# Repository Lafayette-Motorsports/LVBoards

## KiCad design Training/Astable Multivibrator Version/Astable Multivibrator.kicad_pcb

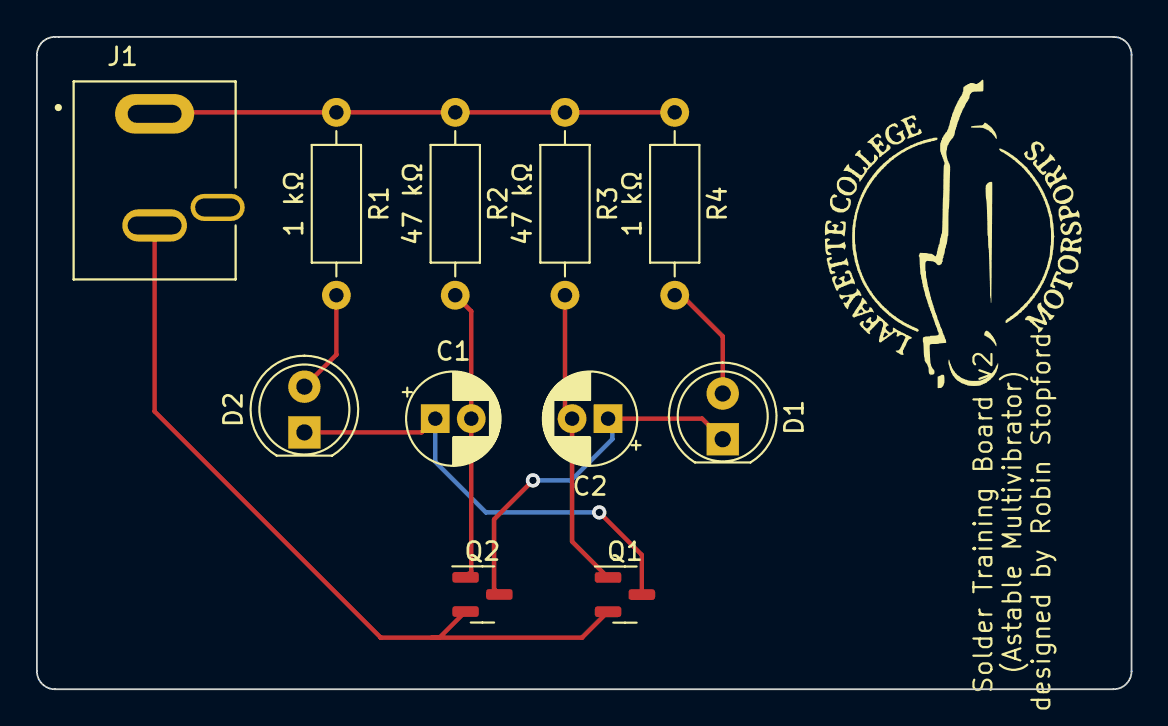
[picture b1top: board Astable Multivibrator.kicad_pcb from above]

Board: 2 copper layers, 60.8 x 36.2 mm, 11 parts (0 on the bottom side), 8 nets.

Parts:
C1, C2: 10uF; CP_Radial_D5.0mm_P2.00mm
D1, D2: LED; LED_D5.0mm
J1: 5V; CUI_PJ-044A
Q1, Q2: MMBT3904; SOT-23
R1, R4: 1 kΩ; R_Axial_DIN0207_L6.3mm_D2.5mm_P10.16mm_Horizontal
R2, R3: 47 kΩ; R_Axial_DIN0207_L6.3mm_D2.5mm_P10.16mm_Horizontal

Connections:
GND: J1.2, Q1.2 (E), Q2.2 (E)
unnamed: D1.2 (A), R4.2
unnamed: C2.1, D1.1 (K), Q2.3 (C)
unnamed: D2.2 (A), R1.2
unnamed: C1.1, D2.1 (K), Q1.3 (C)
unnamed: J1.1, R1.1, R2.1, R3.1, R4.1
unnamed: C2.2, Q1.1 (B), R3.2
unnamed: C1.2, Q2.1 (B), R2.2

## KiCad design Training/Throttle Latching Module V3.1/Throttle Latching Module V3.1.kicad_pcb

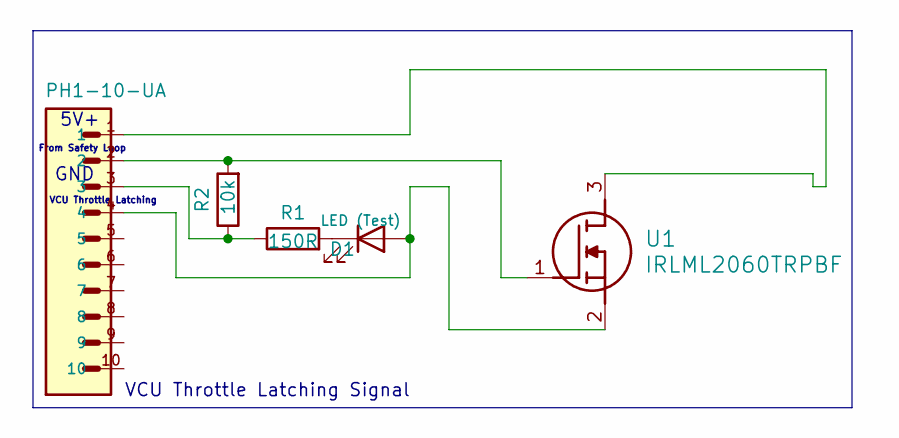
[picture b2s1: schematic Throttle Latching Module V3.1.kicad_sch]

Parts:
D1: LED (Test); LED_0603_1608Metric
J1: PH1-10-UA; JST_PH_B12B-PH-K_1x12_P2.00mm_Vertical
R1: 150R; R_Axial_DIN0204_L3.6mm_D1.6mm_P7.62mm_Horizontal
R2: 10k; R_Axial_DIN0204_L3.6mm_D1.6mm_P7.62mm_Horizontal
U1: IRLML2060TRPBF; SOT95P237X112-3N; Manufacturer_Part_Number IRLML2060TRPBF; Mouser Part Number 942-IRLML2060TRPBF

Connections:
unnamed: D1.2 (A), J1.4, U1.2 (S)
unnamed: D1.1 (K), R1.2
unnamed: J1.3, R1.1, R2.1
unnamed: J1.1, U1.3 (D)
unnamed: J1.2, R2.2, U1.1 (G)

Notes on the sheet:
5V+
VCU Throttle Latching
VCU Throttle Latching Signal
From Safety Loop
GND

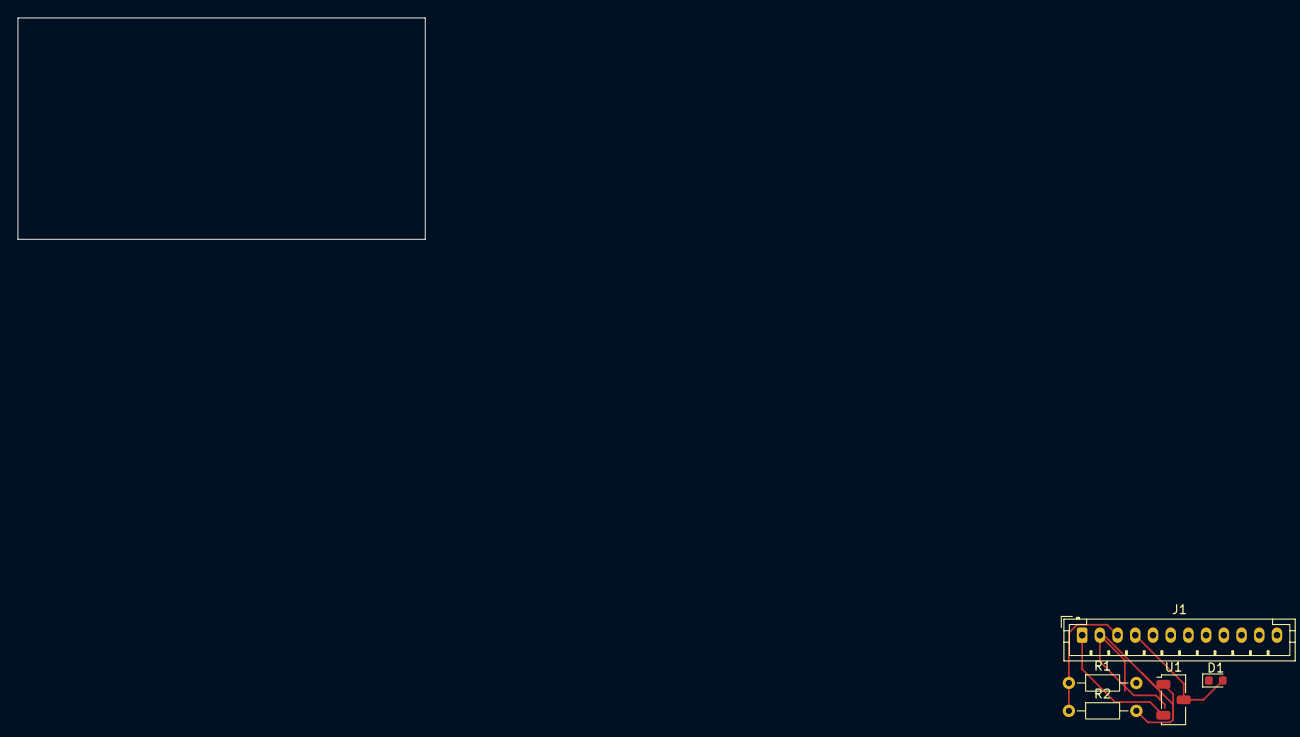
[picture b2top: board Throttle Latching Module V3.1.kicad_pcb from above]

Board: 2 copper layers, 46.0 x 25.0 mm, 5 parts (0 on the bottom side), 5 nets.

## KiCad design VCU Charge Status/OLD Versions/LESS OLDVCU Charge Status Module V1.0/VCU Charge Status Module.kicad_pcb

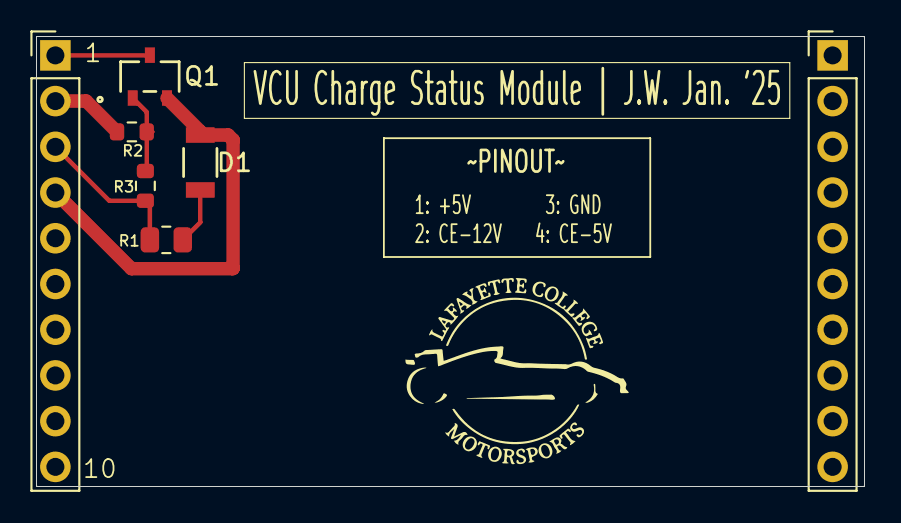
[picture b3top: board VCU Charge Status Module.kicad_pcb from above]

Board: 2 copper layers, 46.0 x 25.0 mm, 7 parts (0 on the bottom side), 5 nets.

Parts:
D1: LED (Test); LED_AP3216SYD_KNB
J1, J1#2: PH1-10-UA; PinHeader_1x10_P2.54mm_Vertical
Q1: AON6411; SOT23_INF
R1: 150R; R_0805_2012Metric
R2, R3: 10k; R_0603_1608Metric

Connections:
unnamed: D1.2 (A), J1.4, Q1.2 (S)
unnamed: D1.1 (K), R1.2
unnamed: J1.2, R2.1
unnamed: J1.3, R1.1, R3.1
unnamed: R2.2, R3.2

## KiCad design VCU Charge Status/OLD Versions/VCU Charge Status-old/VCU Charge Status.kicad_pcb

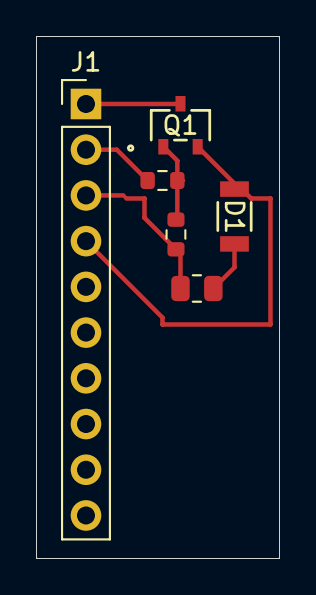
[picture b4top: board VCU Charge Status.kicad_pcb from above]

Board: 2 copper layers, 13.5 x 29.0 mm, 6 parts (0 on the bottom side), 5 nets.

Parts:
D1: LED (Test); LED_AP3216SYD_KNB
J1: PH1-10-UA; PinHeader_1x10_P2.54mm_Vertical
Q1: AON6411; SOT23_INF
R1: 150R; R_0805_2012Metric
R2, R3: 10k; R_0603_1608Metric

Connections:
5v+: J1.1, Q1.3 (S)
From-Safety-Loop-2: Q1.1 (S), R2.2, R3.2
GND: J1.3, R1.1, R3.1
VCU-Throttle-Latching: D1.1 (K), Q1.2 (S)
uuhh: D1.2 (A), R1.2

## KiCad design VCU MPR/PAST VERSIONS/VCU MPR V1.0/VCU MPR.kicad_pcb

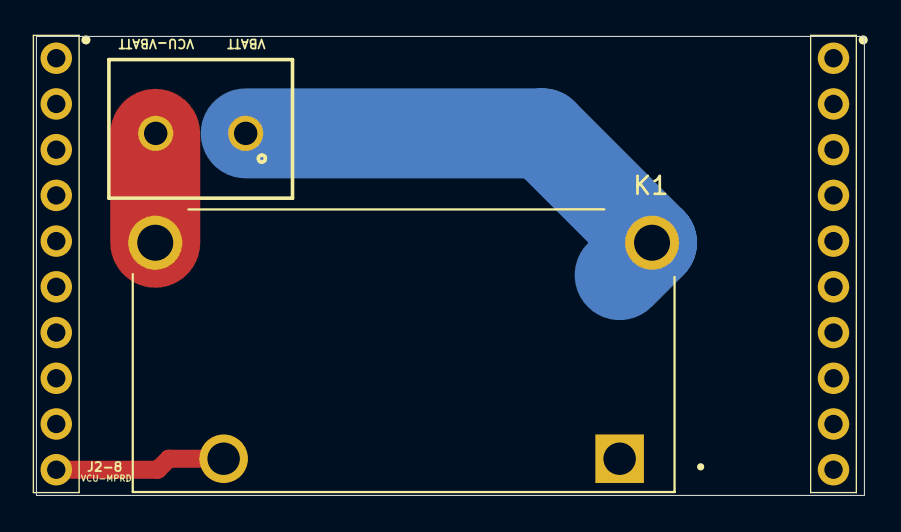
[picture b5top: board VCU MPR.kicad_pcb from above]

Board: 2 copper layers, 46.0 x 25.5 mm, 4 parts (0 on the bottom side), 3 nets.

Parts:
J1: 691137710002
J2, J2#2: PH1-10-UA; 1X10-2.54MM-THT
K1: ALF1PF12; RELAY_ALF1PF12

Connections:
/VBATT: J1.1, K1.1, K1.3
/VCU VBATT: J1.2, K1.4
VCU-MPRD: J2.10, K1.2
